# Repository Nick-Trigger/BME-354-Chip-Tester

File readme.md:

# BME 354 Chip Tester

A custom PCB designed to test analog ICs — specifically the ADC623 and INA126 instrumentation amplifiers — as part of a BME 354 course project.

## Overview

The board provides:

- A sine wave generator signal source
- A regulated voltage supply
- LED indicators for pass/fail output comparison
- Switch-controlled power and signal routing
- Test points for oscilloscope / multimeter probing

## Project Files

| Folder / File | Description |
| --- | --- |
| [KiCad_milling_machine/](KiCad_milling_machine/) | KiCad schematic and PCB layout files (milling-machine spec) |
| [KiCad_milling_machine/Custom Libraries/](KiCad_milling_machine/Custom%20Libraries/) | Custom KiCad symbols and footprints for non-standard parts |
| [Documentation/](Documentation/) | Photos from build and testing stages |
| [Documentation.md](Documentation.md) | Full design log with dated entries and schematic notes |

## Key Schematics

- [ChipTester_354.kicad_sch](KiCad_milling_machine/ChipTester_354.kicad_sch) — top-level schematic
- [AD_INA.kicad_sch](KiCad_milling_machine/AD_INA.kicad_sch) — ADC623 / INA126 test circuit
- [wave_generator.kicad_sch](KiCad_milling_machine/wave_generator.kicad_sch) — sine wave generator sub-circuit
- [pwrsup.kicad_sch](KiCad_milling_machine/pwrsup.kicad_sch) — voltage regulator sub-circuit
- [mcp_if.kicad_sch](KiCad_milling_machine/mcp_if.kicad_sch) — MCP interface sub-circuit

## Design Log

See [Documentation.md](Documentation.md) for a full chronological record of design decisions, breadboard testing, PCB layout, milling, soldering, and troubleshooting.

## Components

Non-standard parts sourced from DigiKey. Custom footprints included in [KiCad_milling_machine/Custom Libraries/](KiCad_milling_machine/Custom%20Libraries/) for:

- `100DP1T2B4M6QE` — DPDT slide switch
- `100SP3T2B4M6RE` — SP3T slide switch
- `7101MD9AQE` — rotary switch
- `BH9VPC` — 9V battery holder
- `PRS12R_4025K_103B1` — potentiometer

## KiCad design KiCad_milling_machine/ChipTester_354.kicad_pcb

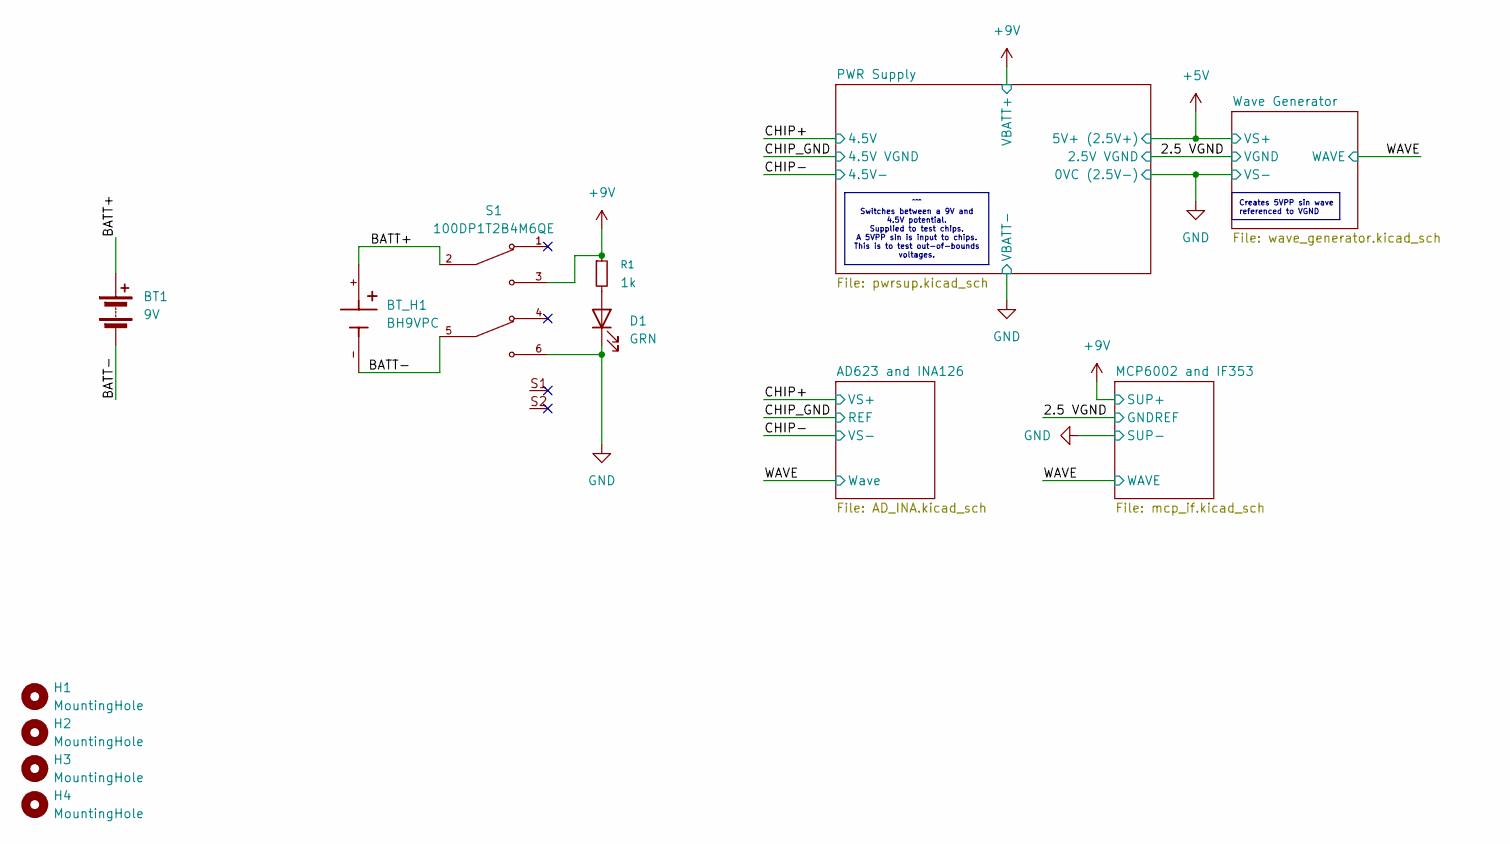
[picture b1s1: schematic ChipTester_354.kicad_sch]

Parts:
BT1: 9V
BT_H1: BH9VPC; BAT_BH9VPC; PARTREV F
D1: GRN; LED_D5.0mm
H1, H2, H3, H4: MountingHole; MountingHole_3.2mm_M3
R1: 1k; R_Axial_DIN0207_L6.3mm_D2.5mm_P7.62mm_Horizontal
S1: 100DP1T2B4M6QE; SW_100DP1T2B4M6QE; PARTREV G

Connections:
+9V: R1.1, S1.3; also elsewhere on the board
/BATT+: BT1.1 (+), BT_H1.+, S1.2
/BATT-: BT1.2 (-), BT_H1.-, S1.5
GND: D1.1 (K), S1.6; also elsewhere on the board
unnamed: D1.2 (A), R1.2

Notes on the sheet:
Creates 5VPP sin wave referenced to VGND
^^^ Switches between a 9V and 4.5V potential. Supplied to test chips. A 5VPP sin is input to chips. This is to test out-of-bounds voltages.

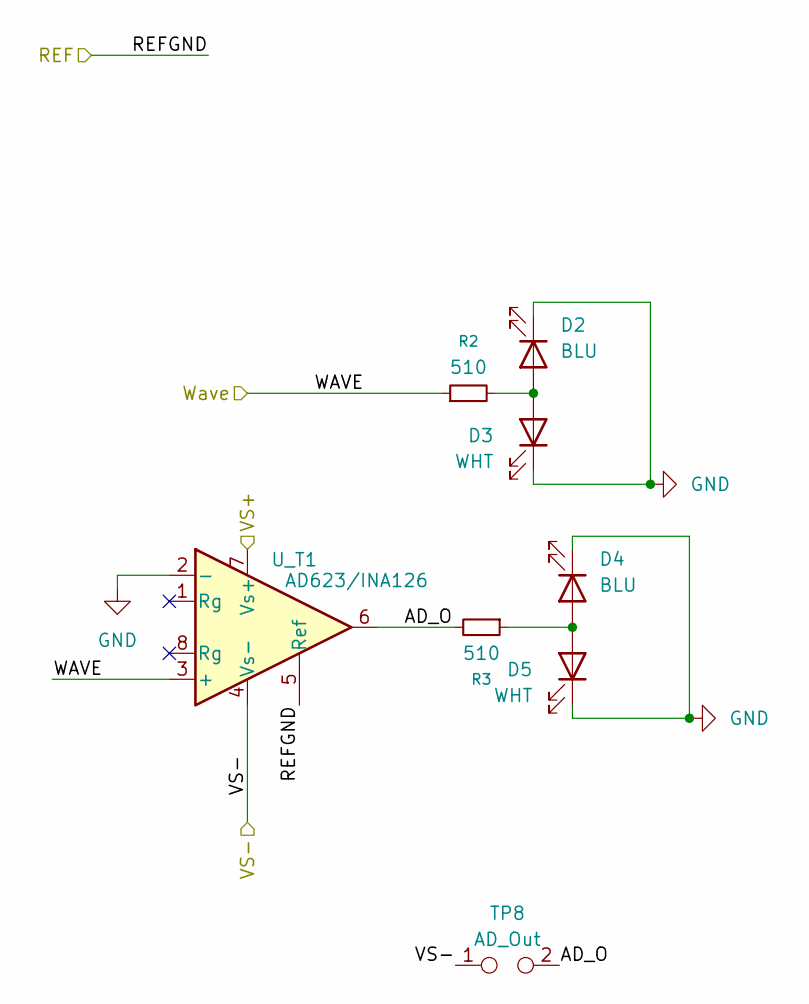
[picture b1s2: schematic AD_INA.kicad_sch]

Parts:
D2, D4: BLU; LED_D5.0mm
D3, D5: WHT; LED_D5.0mm
R2, R3: 510; R_Axial_DIN0207_L6.3mm_D2.5mm_P7.62mm_Horizontal
TP8: AD_Out; PinSocket_1x02_P2.54mm_Vertical
U_T1: AD623/INA126; DIP-8_W7.62mm_Socket

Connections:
+9V: U_T1.7 (Vs+); also elsewhere on the board
/AD623 and INA126/AD_O: R3.2, TP8.2, U_T1.6
/CHIP_GND: U_T1.5 (Ref); also elsewhere on the board
/WAVE: R2.1, U_T1.3 (+); also elsewhere on the board
GND: D2.1 (K), D3.1 (K), D4.1 (K), D5.1 (K), TP8.1, U_T1.2 (-), U_T1.4 (Vs-); also elsewhere on the board
unnamed: D2.2 (A), D3.2 (A), R2.2
unnamed: D4.2 (A), D5.2 (A), R3.1

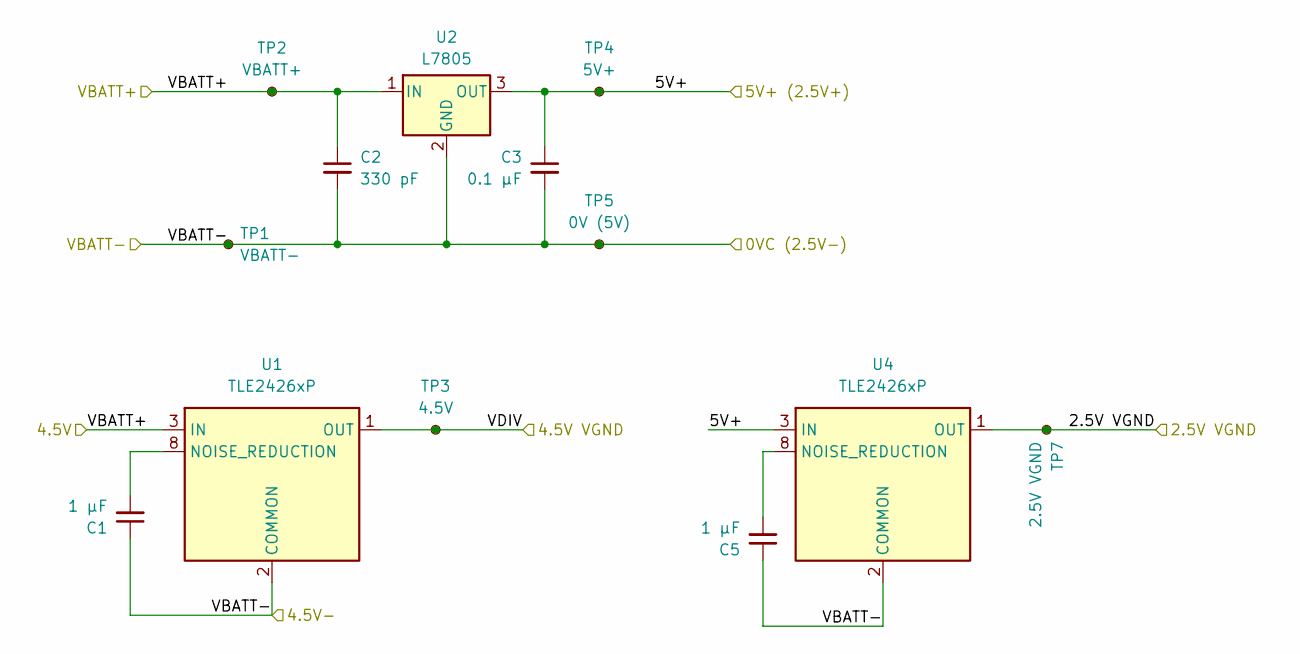
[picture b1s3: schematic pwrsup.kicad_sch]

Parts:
C1, C5: 1 µF; CP_Radial_D5.0mm_P2.00mm
C2: 330 pF; C_Disc_D5.0mm_W2.5mm_P2.50mm
C3: 0.1 µF; C_Disc_D5.0mm_W2.5mm_P2.50mm
TP1: VBATT-; TestPoint_Pad_D2.0mm
TP2: VBATT+; TestPoint_Pad_D2.0mm
TP3: 4.5V; TestPoint_Pad_D2.0mm
TP4: 5V+; TestPoint_Pad_D2.0mm
TP5: 0V (5V); TestPoint_Pad_D2.0mm
TP7: 2.5V VGND; TestPoint_Pad_D2.0mm
U1, U4: TLE2426xP; DIP-8_W7.62mm
U2: L7805; TO-220-3_Horizontal_TabDown

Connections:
+5V: C3.1, TP4.1, U2.3 (OUT), U4.3 (IN); also elsewhere on the board
+9V: C2.1, TP2.1, U1.3 (IN), U2.1 (IN); also elsewhere on the board
/2.5 VGND: TP7.1, U4.1 (OUT); also elsewhere on the board
/CHIP_GND: TP3.1, U1.1 (OUT); also elsewhere on the board
GND: C1.1, C2.2, C3.2, C5.1, TP1.1, TP5.1, U1.2 (COMMON), U2.2 (GND), U4.2 (COMMON); also elsewhere on the board
unnamed: C1.2, U1.8 (NOISE_REDUCTION)
unnamed: C5.2, U4.8 (NOISE_REDUCTION)

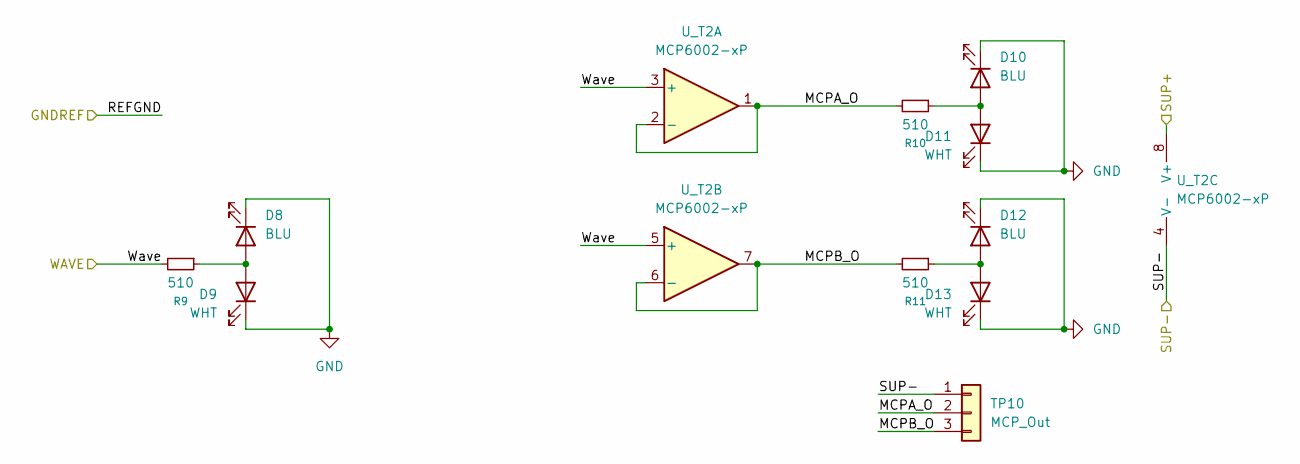
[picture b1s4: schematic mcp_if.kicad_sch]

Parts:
D8, D10, D12: BLU; LED_D5.0mm
D9, D11, D13: WHT; LED_D5.0mm
R9, R10, R11: 510; R_Axial_DIN0207_L6.3mm_D2.5mm_P7.62mm_Horizontal
TP10: MCP_Out; PinSocket_1x03_P2.54mm_Vertical
U_T2: MCP6002-xP; DIP-8_W7.62mm_Socket

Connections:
+9V: U_T2.8 (V+); also elsewhere on the board
/MCP6002 and IF353/MCPA_O: R10.2, TP10.2, U_T2.1, U_T2.2 (-)
/MCP6002 and IF353/MCPB_O: R11.2, TP10.3, U_T2.6 (-), U_T2.7
/WAVE: R9.2, U_T2.3 (+), U_T2.5 (+); also elsewhere on the board
GND: D8.1 (K), D9.1 (K), D10.1 (K), D11.1 (K), D12.1 (K), D13.1 (K), TP10.1, U_T2.4 (V-); also elsewhere on the board
unnamed: D8.2 (A), D9.2 (A), R9.1
unnamed: D10.2 (A), D11.2 (A), R10.1
unnamed: D12.2 (A), D13.2 (A), R11.1

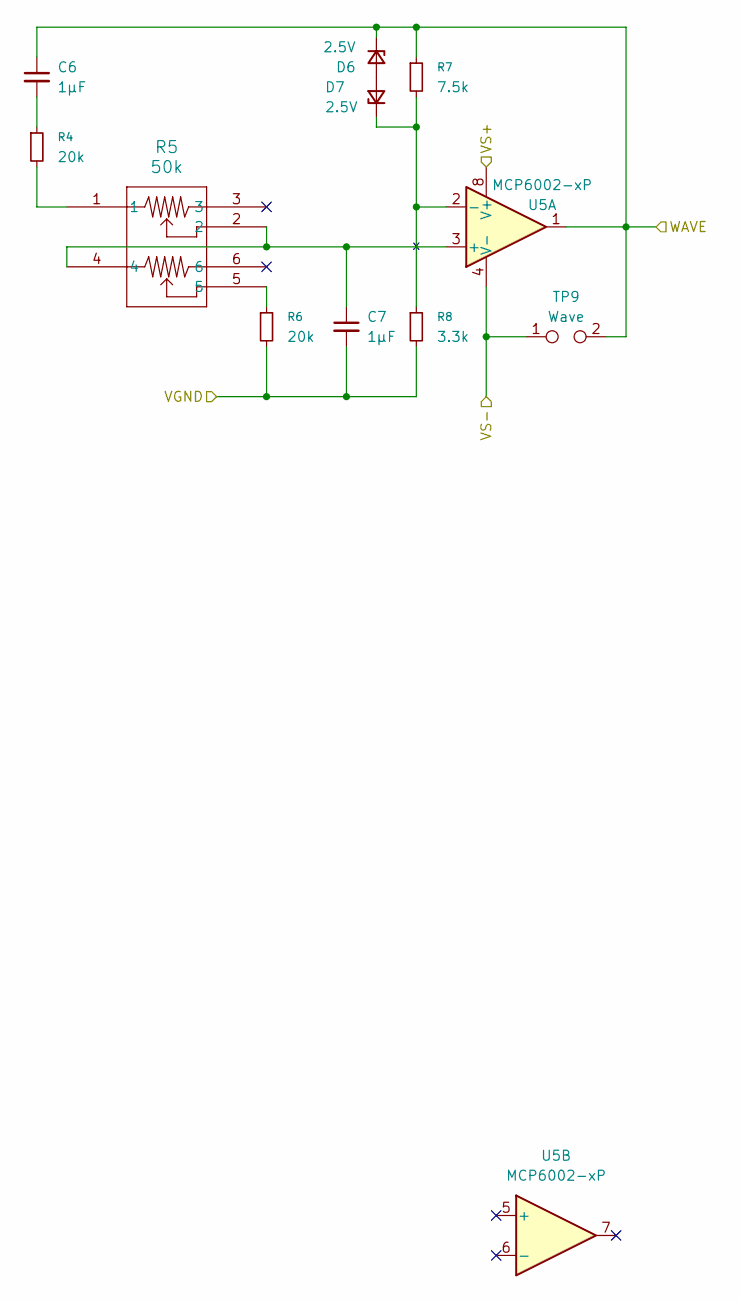
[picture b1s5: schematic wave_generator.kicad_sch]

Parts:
C6, C7: 1µF; C_Disc_D5.0mm_W2.5mm_P2.50mm
D6, D7: 2.5V; D_DO-35_SOD27_P7.62mm_Horizontal
R4, R6: 20k; R_Axial_DIN0207_L6.3mm_D2.5mm_P7.62mm_Horizontal
R5: 50k; PRS12R-4_BRN
R7: 7.5k; R_Axial_DIN0207_L6.3mm_D2.5mm_P7.62mm_Horizontal
R8: 3.3k; R_Axial_DIN0207_L6.3mm_D2.5mm_P7.62mm_Horizontal
TP9: Wave; PinSocket_1x02_P2.54mm_Vertical
U5: MCP6002-xP; DIP-8_W7.62mm

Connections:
+5V: U5.8 (V+); also elsewhere on the board
/2.5 VGND: C7.2, R6.2, R8.2; also elsewhere on the board
/WAVE: C6.1, D6.1 (K), R7.1, TP9.2, U5.1; also elsewhere on the board
GND: TP9.1, U5.4 (V-); also elsewhere on the board
unnamed: C6.2, R4.1
unnamed: D6.2 (A), D7.2 (A)
unnamed: D7.1 (K), R7.2, R8.1, U5.2 (-)
unnamed: R4.2, R5.1
unnamed: R5.5, R6.1
unnamed: C7.1, R5.2, R5.4, U5.3 (+)

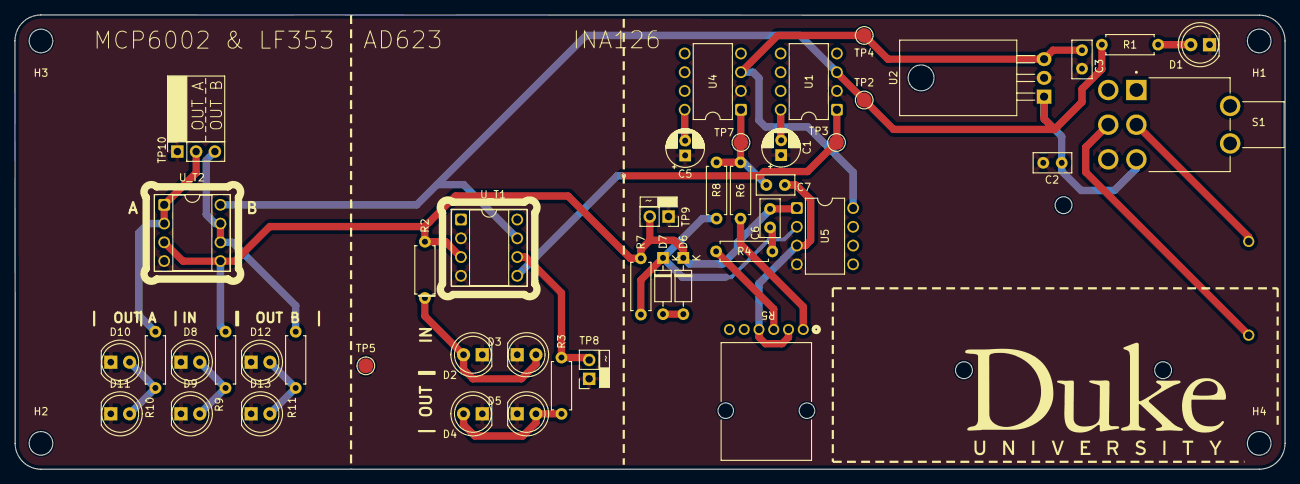
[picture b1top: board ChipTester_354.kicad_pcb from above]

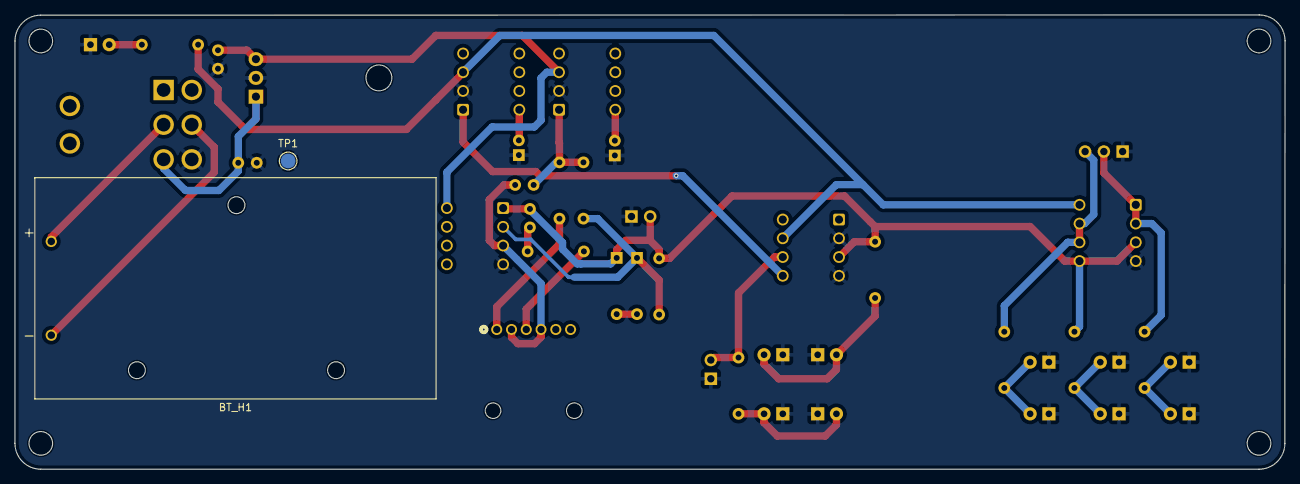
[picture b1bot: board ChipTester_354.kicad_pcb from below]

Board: 2 copper layers, 172.0 x 61.5 mm, 51 parts (2 on the bottom side), 25 nets.

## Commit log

2025-05-19 tetsing alicias git connection to repo
2025-05-19 Adding documentation file
2025-05-19 Added KiCad Docs and started working
2025-05-20 Finish power supply, make waveform generator.
2025-05-20 changed date
2025-05-21 added documentation for Day 2
2025-05-21 added Documentation Images Folder
2025-05-21 changed resistance on schematic for minimum reisstance of 20kOhm
2025-05-28 changed resistor values after testing
2025-05-28 Change to TI rail splitter.
2025-05-28 Swapped mcp6002 rail splitter for TI TLE2426xP
2025-05-28 started edited pcb layout
2025-05-28 ADD AC623 and INA126 Test Circuitry
2025-05-28 added footprints to schematic
2025-05-28 Update battery switch to dpdt.
2025-05-28 Add power led
2025-05-29 updated footprint to be all THT, battery holder still not there
2025-05-29 Some TP -> Headers, added footprints, fixed battery footprint, started layout of board.
2025-05-30 Made the board :D
2025-06-02 Added annotations to pcb
2025-06-04 added second kicad proejct folder
2025-06-04 adding to pull
2025-06-04 Added milling machine files / updated schematic+pcb annotations / updated footprints
2025-06-08 Add PCB Image
2025-06-10 re-edited for 2nd milling, fixing clearances and problem areas
2025-06-30 Updated Documentation
2025-07-25 Removed Switch
2025-07-25 Updated Documentation with Info on Schematic Labelling
2025-07-25 Ground inverting input of AD/INA circuit
2025-08-04 grounded LEDs to allow for sufficient voltage blinking difference
2025-08-04 updated documentation and removed old milling files
2025-08-11 deleted old version, milling machine folder is reflective of most recent chip design
2026-05-12 Add initial README file
